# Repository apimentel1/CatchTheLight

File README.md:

# Catch The Light Project
This game is based off of the popular arcade game Cyclone. For our Junior Design Project, we created a handheld version of the game on a PCB.

### [Department Page](https://www.umassd.edu/engineering/ece/)
UMASS Dartmouth ECE department page - This page has information reguarding UMASS Dartmouth's Electrical and Computer Engineering Program.

### [Documentation of Design Challenge](https://github.com/apimentel1/CatchTheLight/blob/master/Documentation/Documentation_of_Design_Challenge.md)
The Documentation of Design Challenge gives insight into the process taken to complete the project. The documentation includes the data sheets referenced, resources used, and some of the challenges that arose along the way.

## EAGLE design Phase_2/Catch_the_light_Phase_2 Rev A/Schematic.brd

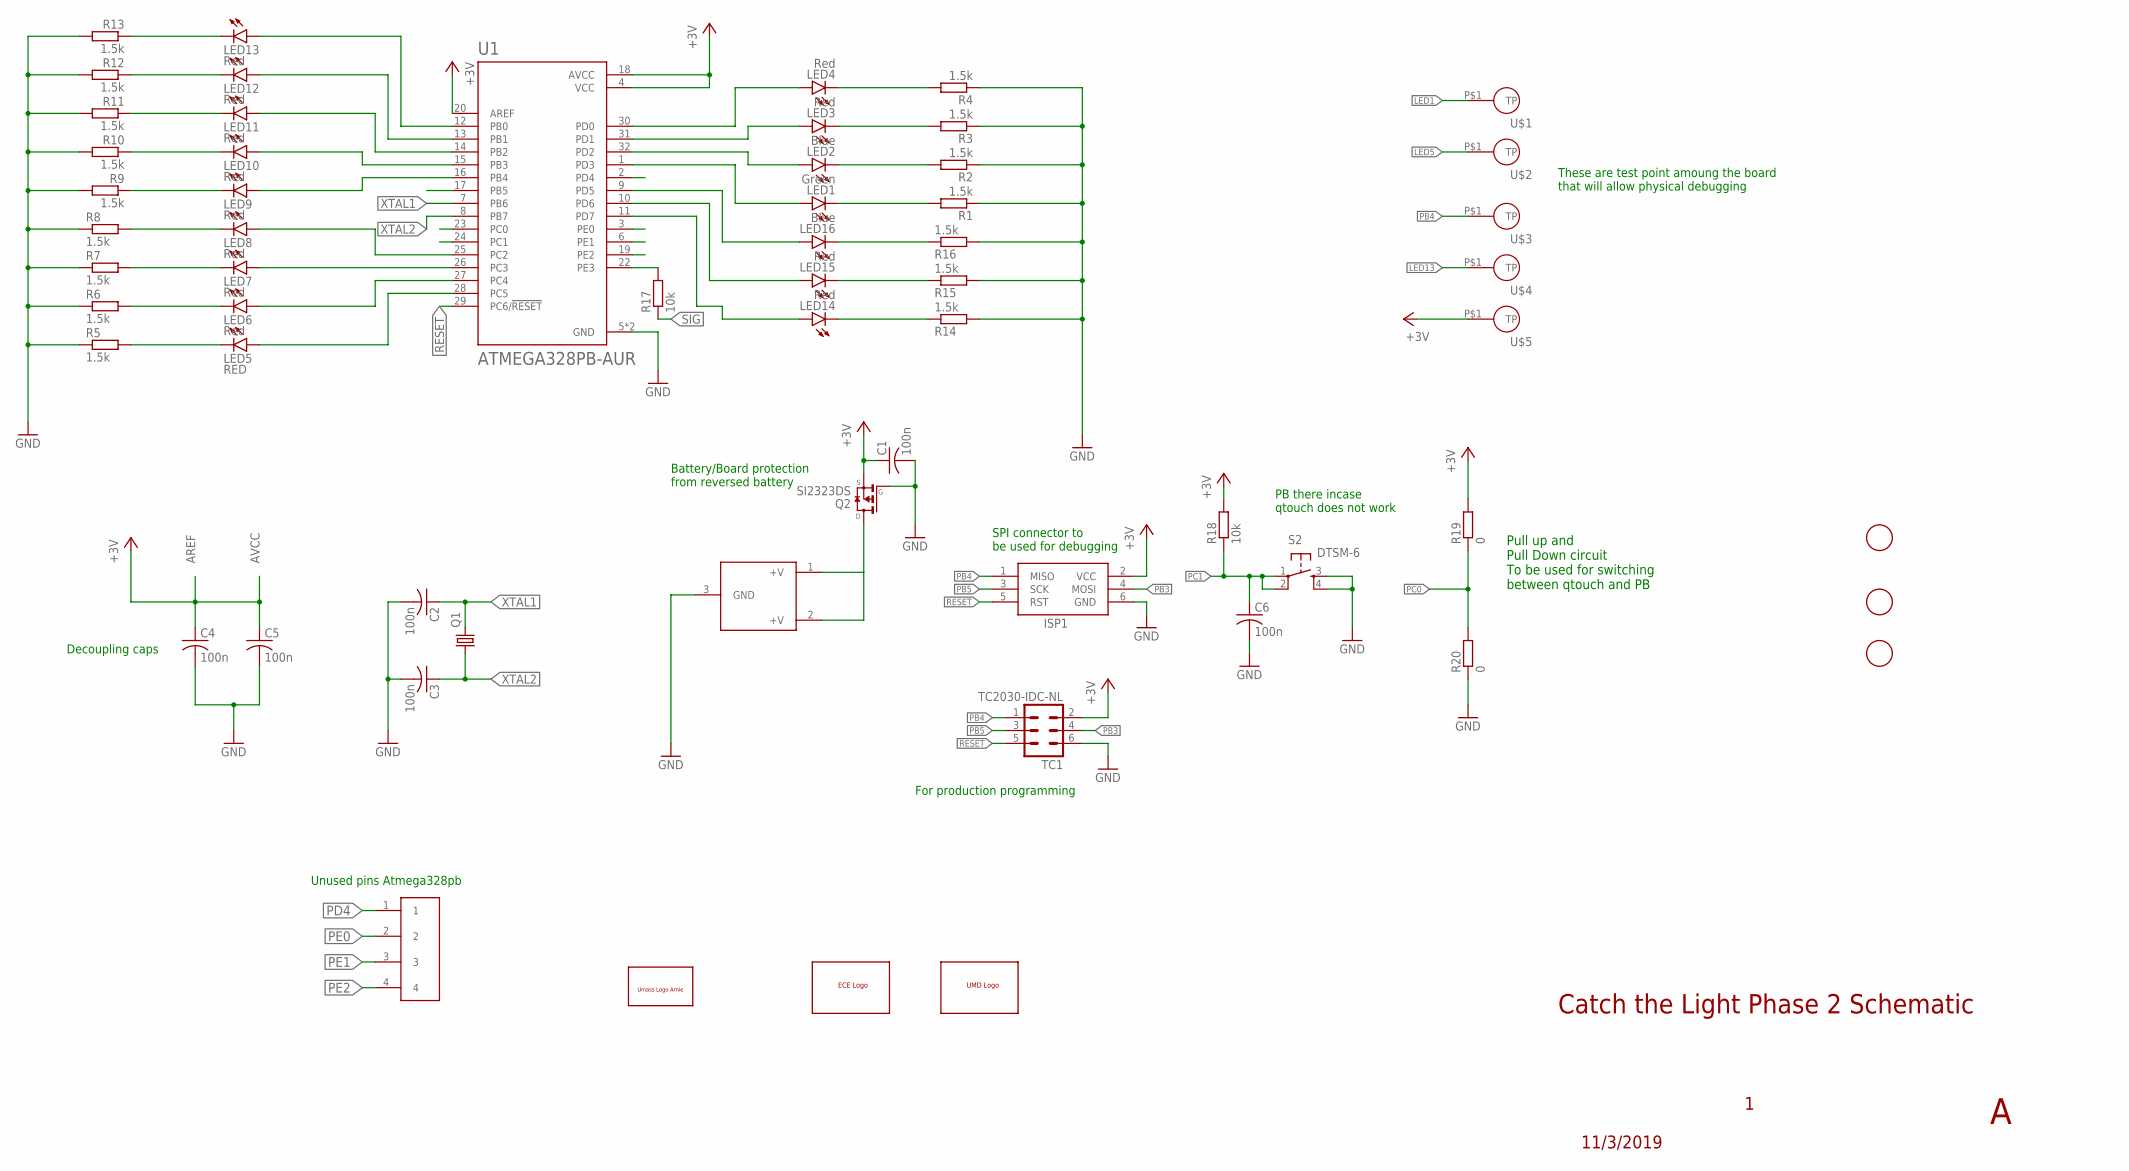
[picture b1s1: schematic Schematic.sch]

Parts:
C1, C2, C3, C4, C5, C6: 100n; C0805
CR2032: BC-2003SMD; BC-2003
ISP1: AVRISP-6; AVRISP
LED1: Green; CHIP-LED0805
LED2, LED16: Blue; CHIP-LED0805
LED3, LED4, LED6, LED7, LED8, LED9, LED10, LED11, LED12, LED13, LED14, LED15: Red; CHIP-LED0805
LED5: RED; CHIP-LED0805
Q1: CRYSTALHC49UP; HC49UP
Q2: SI2323DS; SOT23
R1, R2, R3, R4, R5, R6, R7, R8, R9, R10, R11, R12, R13, R14, R15, R16: 1.5k; R0805
R17, R18: 10k; R0805
R19, R20: 0; R0805
S2: DTSM-6
TC1: TC2030-IDC-NL
U1: ATMEGA328PB-AUR; QFP80P900X900X120-32N
U$1, U$2, U$3, U$4, U$5: TEST_POINT
U$6: PINHEADER; HEADERPIN
U$7, U$8, U$9: FIDUCIAL; FIDUCIAL_1MM
U$10: UMASSLGOARNIE; UMASSLOGOARNIE
U$11: ECE_LOGO; ECE
U$12: UMDLOGO

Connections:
+3V3: C1.1, C4.1, C5.1, ISP1.2 (VCC), Q2.2 (S), R18.2, R19.2, TC1.2, U1.4 (VCC), U1.18 (AVCC), U1.20 (AREF), U$5.P$1
GND: C1.2, C2.2, C3.2, C4.2, C5.2, C6.2, CR2032.3 (GND), ISP1.6 (GND), Q2.1 (G), R1.1, R2.1, R3.1, R4.1, R5.1, R6.1, R7.1, R8.1, R9.2, R10.2, R11.2, R12.2, R13.2, R14.2, R15.2, R16.2, R20.1, S2.3, S2.4, TC1.6, U1.5 (GND), U1.21 (GND)
LED1: LED1.A, U1.1 (PD3), U$1.P$1
LED5: LED5.A, U1.28 (PC5), U$2.P$1
LED12: LED12.A, U1.13 (PB1)
LED13: LED13.A, U1.12 (PB0), U$4.P$1
unnamed: LED5.C, R5.2
unnamed: CR2032.1 (+V), CR2032.2 (+V), Q2.3 (D)
unnamed: LED11.A, U1.14 (PB2)
unnamed: LED6.A, U1.27 (PC4)
unnamed: LED8.A, U1.25 (PC2)
unnamed: LED7.A, U1.26 (PC3)
unnamed: LED4.A, U1.30 (PD0)
unnamed: LED3.A, U1.31 (PD1)
unnamed: LED2.A, U1.32 (PD2)
unnamed: LED16.A, U1.9 (PD5)
unnamed: LED15.A, U1.10 (PD6)
unnamed: LED14.A, U1.11 (PD7)
unnamed: LED9.C, R9.1
unnamed: R17.2, U1.22 (PE3)
unnamed: LED8.C, R8.2
unnamed: LED7.C, R7.2
unnamed: LED6.C, R6.2
unnamed: LED4.C, R4.2
unnamed: LED3.C, R3.2
unnamed: LED2.C, R2.2
unnamed: LED1.C, R1.2
unnamed: LED10.C, R10.1
unnamed: LED11.C, R11.1
unnamed: LED12.C, R12.1
unnamed: LED13.C, R13.1
unnamed: LED14.C, R14.1
unnamed: LED15.C, R15.1
unnamed: LED16.C, R16.1
PB3: ISP1.4 (MOSI), LED10.A, TC1.4, U1.15 (PB3)
PB4: ISP1.1 (MISO), LED9.A, TC1.1, U1.16 (PB4), U$3.P$1
PB5: ISP1.3 (SCK), TC1.3, U1.17 (PB5)
PC0: R19.1, R20.2, U1.23 (PC0)
PC1: C6.1, R18.1, S2.1, S2.2, U1.24 (PC1)
PD4: U1.2 (PD4), U$6.1
PE0: U1.3 (PE0), U$6.2
PE1: U1.6 (PE1), U$6.3
PE2: U1.19 (PE2), U$6.4
RESET: ISP1.5 (RST), TC1.5, U1.29 (PC6/!RESET)
SIG: R17.1
XTAL1: C2.1, Q1.2, U1.7 (PB6)
XTAL2: C3.1, Q1.1, U1.8 (PB7)

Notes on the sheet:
AREF
AVCC
11/3/2019
Catch the Light Phase 2 Schematic
Pull up and Pull Down circuit To be used for switching between qtouch and PB
PB there incase qtouch does not work
SPI connector to be used for debugging
These are test point amoung the board that will allow physical debugging
For production programming
Battery/Board protection from reversed battery
Decoupling caps
Unused pins Atmega328pb

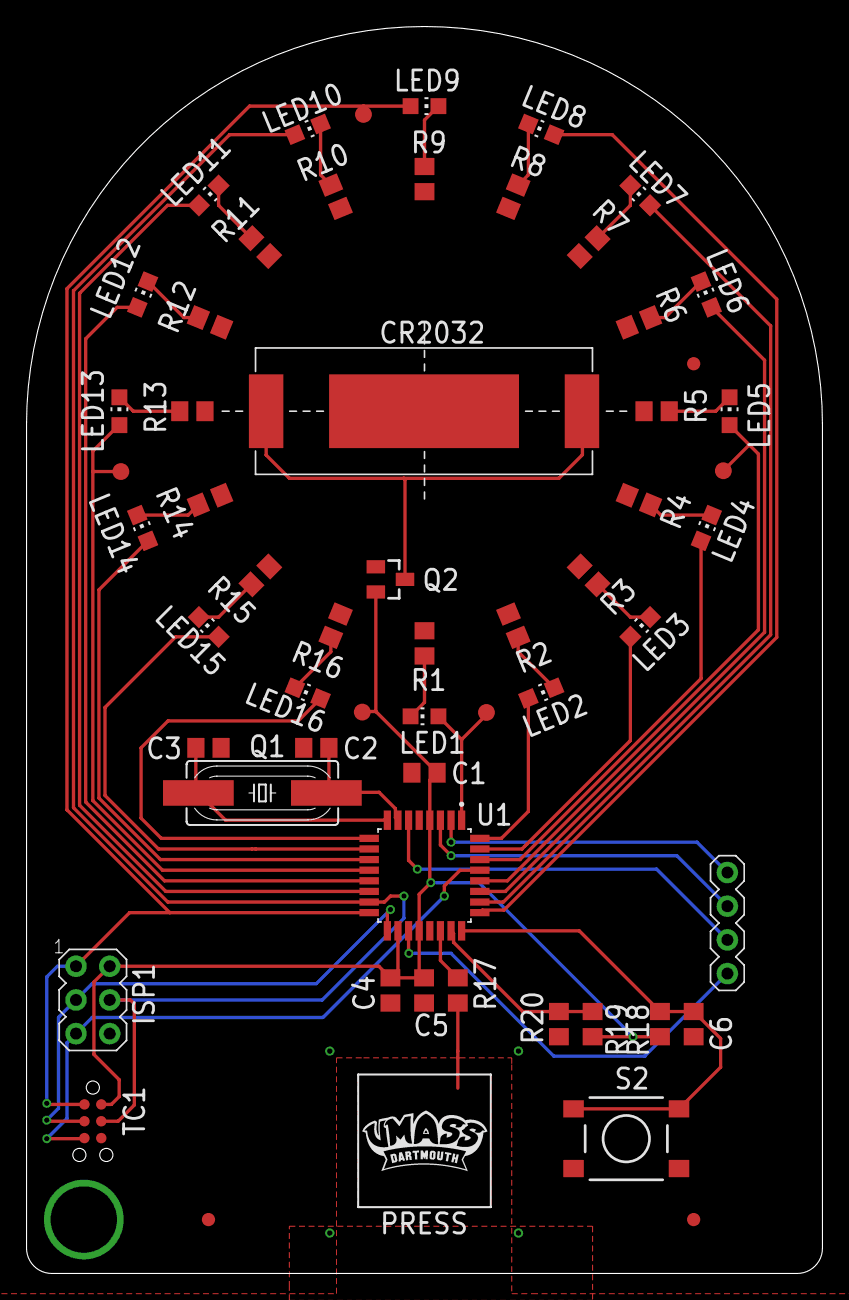
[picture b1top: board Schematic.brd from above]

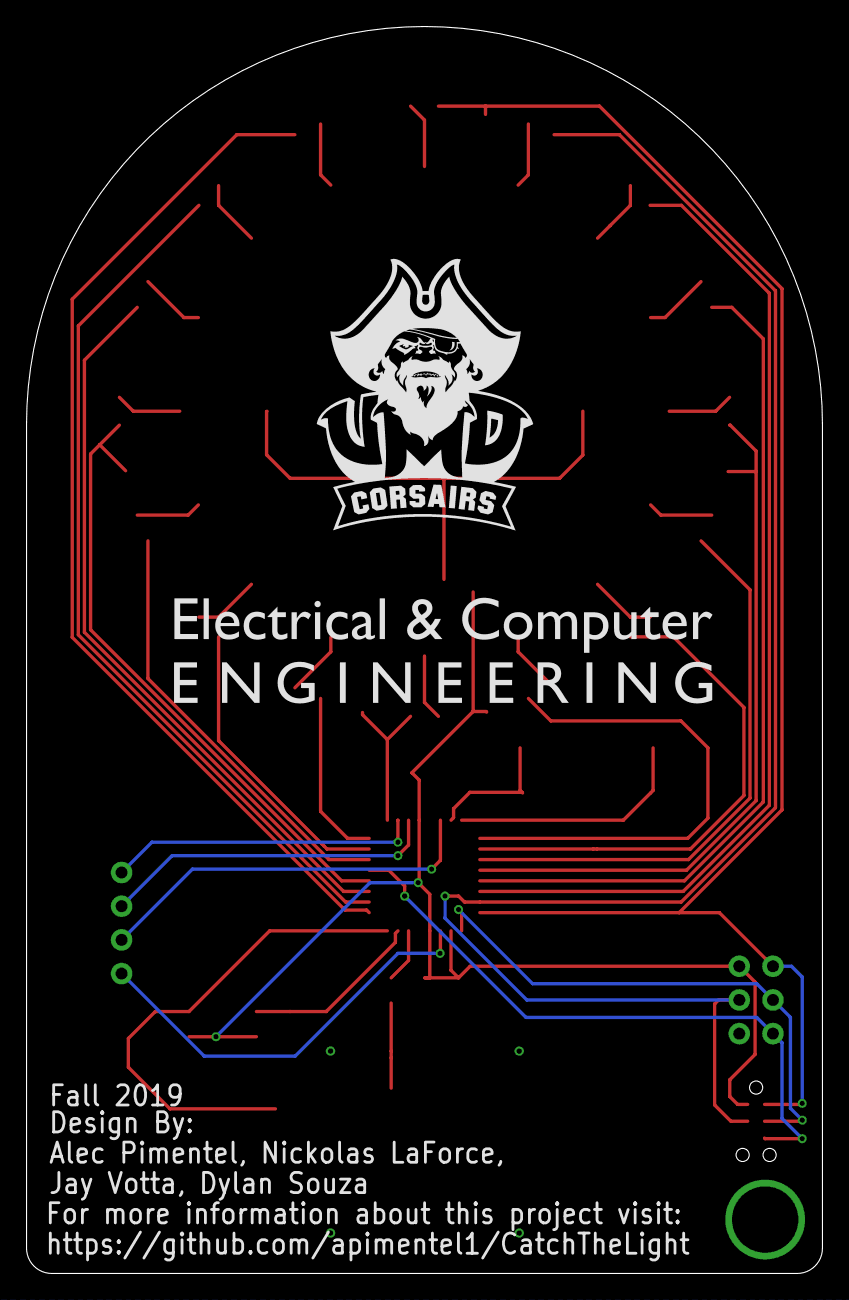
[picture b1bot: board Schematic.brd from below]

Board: 2 copper layers, 60.0 x 94.0 mm, 61 parts (2 on the bottom side), 46 nets.

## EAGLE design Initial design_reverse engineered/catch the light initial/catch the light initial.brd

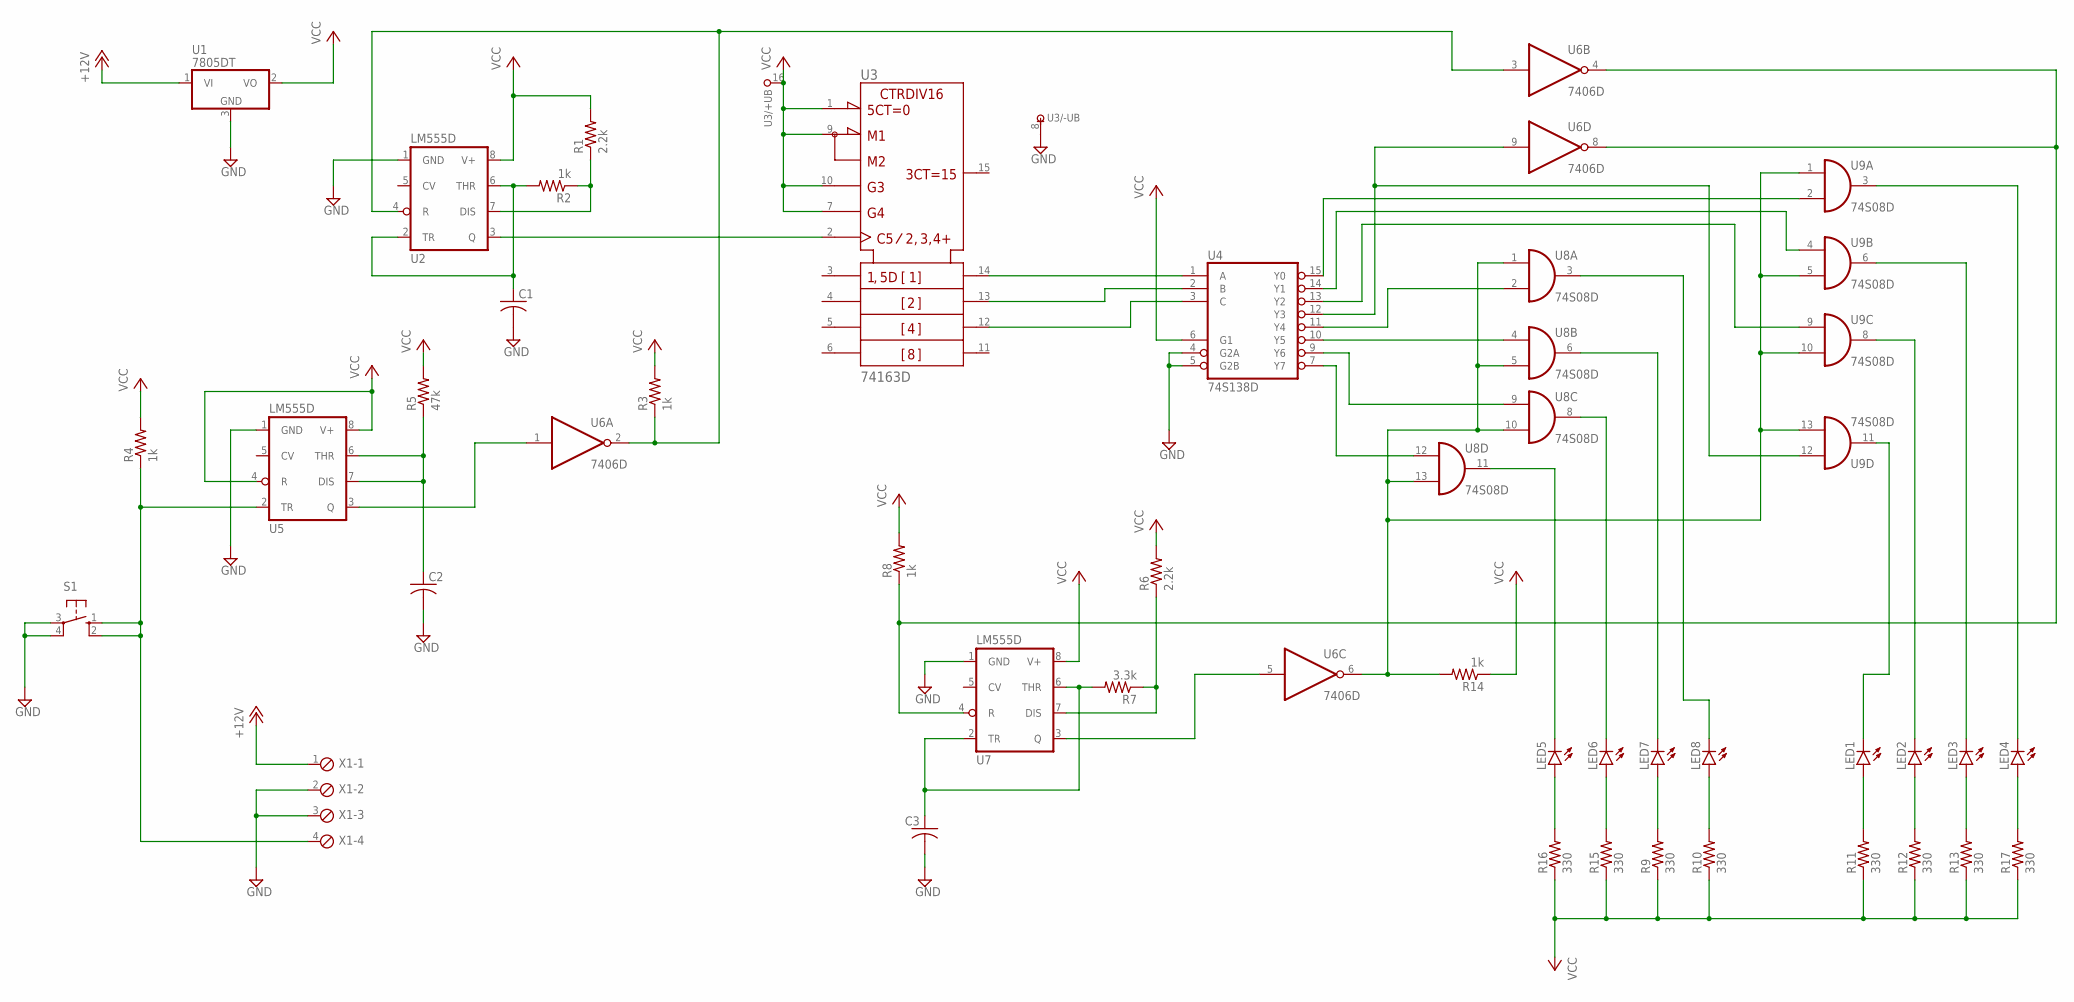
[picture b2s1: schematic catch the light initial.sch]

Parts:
C1, C2, C3: C-USC0805; C0805
LED1, LED2, LED3, LED4, LED5, LED6, LED7, LED8: LEDCHIP-LED0805; CHIP-LED0805
R1, R6: 2.2k; R0805
R2, R3, R4, R8, R14: 1k; R0805
R5: 47k; R0805
R7: 3.3k; R0805
R9, R10, R11, R12, R13, R15, R16, R17: 330; R0805
S1: 10-XX; B3F-10XX
U1: 7805DT; TO252
U2, U5, U7: LM555D; SO08
U3: 74163D; SO16
U4: 74S138D; SO16
U6: 7406D; SO14
U8, U9: 74S08D; SO14
X1: MPT4; 4POL254

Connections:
+12V: U1.1 (VI), X1.1
GND: C1.2, C2.2, C3.2, S1.3, S1.4 (P1), U1.3 (GND), U2.1 (GND), U3.8 (-UB), U4.4 (G2A), U4.5 (G2B), U4.8 (GND), U5.1 (GND), U6.7 (GND), U7.1 (GND), U8.7 (GND), U9.7 (GND), X1.2, X1.3
unnamed: C1.1, R2.2, U2.2 (TR), U2.6 (THR)
unnamed: U2.3 (Q), U3.2 (CLK)
unnamed: R3.1, U2.4 (R), U6.2 (O), U6.3 (I)
unnamed: C2.1, R5.1, U5.6 (THR), U5.7 (DIS)
unnamed: R1.1, R2.1, U2.7 (DIS)
unnamed: U3.14 (QA), U4.1 (A)
unnamed: U5.3 (Q), U6.1 (I)
unnamed: U3.13 (QB), U4.2 (B)
unnamed: U3.12 (QC), U4.3 (C)
unnamed: U4.7 (Y7), U8.12 (I0)
unnamed: U4.9 (Y6), U8.9 (I0)
unnamed: U4.10 (Y5), U8.4 (I0)
unnamed: U4.11 (Y4), U8.2 (I1)
unnamed: U4.12 (Y3), U6.9 (I), U9.12 (I0)
unnamed: U4.15 (Y0), U9.2 (I1)
unnamed: U4.13 (Y2), U9.9 (I0)
unnamed: U4.14 (Y1), U9.4 (I0)
unnamed: R8.1, U6.4 (O), U6.8 (O), U7.4 (R)
unnamed: C3.1, R7.2, U7.2 (TR), U7.6 (THR)
unnamed: R4.1, S1.1 (S), S1.2 (S1), U5.2 (TR), X1.4
unnamed: U6.5 (I), U7.3 (Q)
unnamed: LED5.C, U8.11 (O)
unnamed: R14.2, U6.6 (O), U8.1 (I0), U8.5 (I1), U8.10 (I1), U8.13 (I1), U9.1 (I0), U9.5 (I1), U9.10 (I1), U9.13 (I1)
unnamed: LED6.C, U8.8 (O)
unnamed: LED7.C, U8.6 (O)
unnamed: LED8.C, U8.3 (O)
unnamed: LED1.C, U9.11 (O)
unnamed: LED2.C, U9.8 (O)
unnamed: LED3.C, U9.6 (O)
unnamed: LED4.C, U9.3 (O)
unnamed: LED5.A, R16.2
unnamed: LED6.A, R15.2
unnamed: LED7.A, R9.2
unnamed: LED4.A, R17.2
unnamed: LED8.A, R10.2
unnamed: LED1.A, R11.2
unnamed: LED2.A, R12.2
unnamed: LED3.A, R13.2
unnamed: R6.1, R7.1, U7.7 (DIS)
VCC: R1.2, R3.2, R4.2, R5.2, R6.2, R8.2, R9.1, R10.1, R11.1, R12.1, R13.1, R14.1, R15.1, R16.1, R17.1, U1.2 (VO), U2.8 (V+), U3.1 (!CLR), U3.7 (ENP), U3.9 (!LOAD), U3.10 (ENT), U3.16 (+UB), U4.6 (G1), U4.16 (VCC), U5.4 (R), U5.8 (V+), U6.14 (VCC), U7.8 (V+), U8.14 (VCC), U9.14 (VCC)

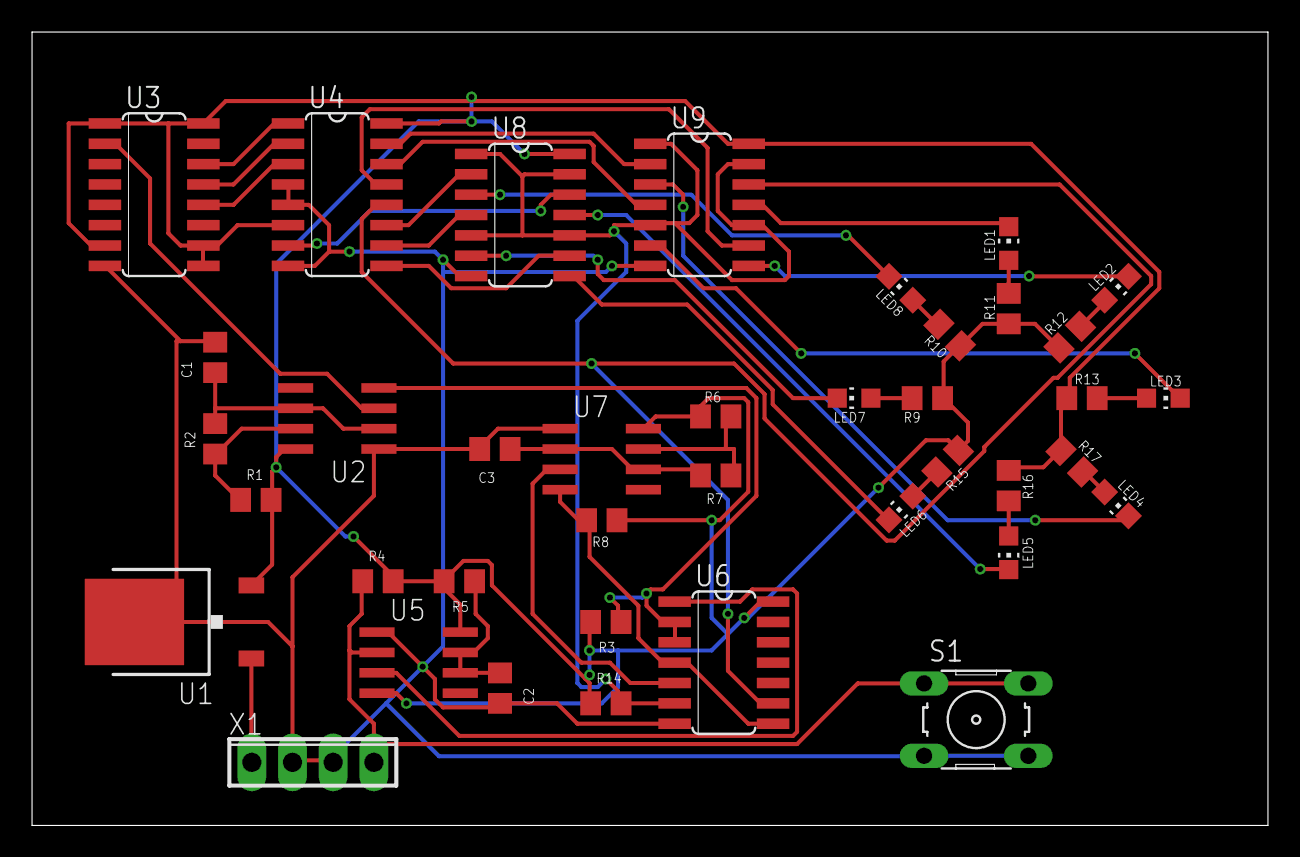
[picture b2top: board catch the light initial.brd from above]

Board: 2 copper layers, 77.1 x 49.5 mm, 39 parts (0 on the bottom side), 42 nets.

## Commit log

2019-10-19 Added Code
2019-10-24 Change delay time
2019-10-24 Data sheet folder
2019-10-25 Tag connector data sheet
2019-10-26 Started to update code for current PCB layout
2019-10-26 reversed the direction, leds can go in both directions
2019-10-27 Add comments
2019-10-28 Added test folder
2019-10-29 Added qtouch documents
2019-10-29 Added xplain-mini wiring diagram
2019-11-03 Create temp
    Reverse engineered layout with surface mount
2019-11-03 Made changes
2019-11-03 Phase 2 PCB design
2019-11-03 Added eagle file
2019-11-04 Added Fritzing Breadboard PDF.
2019-11-04 Add files via upload
    Latest schematic pdf
2019-11-07 Update cams
2019-11-07 Added the new version of the eagle file
2019-11-07 Rename Bom_HTML to Bom_HTML.md
2019-11-10 Added updated compressed zips
2019-11-11 Create Bill of Material
2019-11-11 Add files via upload
    B.O.M for 100 units
2019-11-11 Removed
2019-11-11 Looks good
2019-11-11 Most current version of the board
2019-11-12 Added BoardLayout
2019-11-14 Added new gerbers
2019-11-21 Added atmel start config
2019-11-26 Changed code
2019-11-26 Added u file
2019-11-26 added testqt
2019-11-30 Cleaned up repo
2019-11-30 Added photos
2019-11-30 Renamed pictures
2019-12-01 Game works with a Push Button and LED are at full brightness
2019-12-01 Remove unused code
2019-12-01 Trying to figure out how qTouch works
    Not sure why USART needs to be used with qTouch, need to figure out as it effects the led on PD2
2019-12-04 Updates code that is running with push button on PCB
2019-12-05 add code to test current
2019-12-05 Sony CR2032 Battery Datasheet
2019-12-06 Not much progress
2019-12-11 Added qtouch project
2019-12-11 Leds cycle at right speed and cap touch works
2019-12-11 Remove testqt
2019-12-11 Change delay time from 20ms back to 100ms
2019-12-11 attemmpting to fix led staying on problem
2019-12-12 no progress
2019-12-12 Start of report
    Not sure what else to add.
2019-12-12 Mulitsim Design File
2019-12-12 add working code (1MHZ-josh-branch)
2019-12-13 rearrange to avoid led staying on
2019-12-13 Added comments
2019-12-13 Added pictures
2019-12-13 Updated read me
2019-12-13 added test code for button response time
2019-12-13 added a "sleep" mode
2019-12-14 qtouch update
2019-12-14 added pdf of markdown
2019-12-17 updated catch the light code for pushbutton
2019-12-17 Add pushbutton option
2019-12-18 add push button code
